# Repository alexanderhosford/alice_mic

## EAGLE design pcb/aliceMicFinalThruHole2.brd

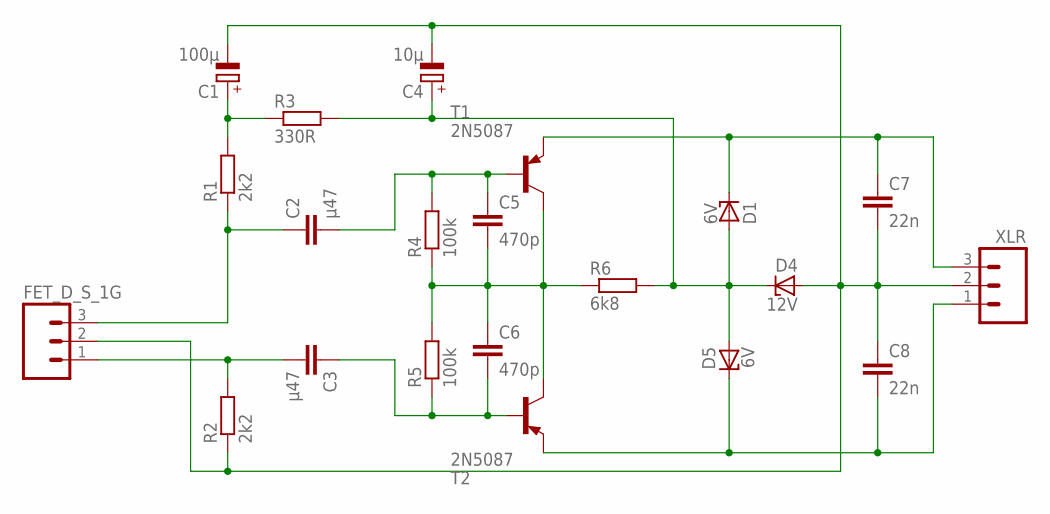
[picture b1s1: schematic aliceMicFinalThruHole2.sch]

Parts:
C1: 100µ; E3,5-8
C2, C3: µ47; C050-045X075
C4: 10µ; E2-4
C5, C6: 470p; C025-024X044
C7, C8: 22n; C025-024X044
D1, D5: 6V; ZD-5-SMALLSILK
D4: 12V; ZD-5-SMALLSILK
FET_D_S_1G: M033.5MM-PADS; 3.5MM_PADS
R1, R2: 2k2; 0207/2V
R3: 330R; 0207/2V
R4, R5: 100k; 0207/2V
R6: 6k8; 0207/2V
T1, T2: 2N5087; TO92-EBC
XLR: M033.5MM-PADS; 3.5MM_PADS

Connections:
GND: C1.-, C4.-, C7.2, C8.1, D4.A, FET_D_S_1G.2, R2.1, XLR.2
unnamed: C4.+, D1.A, D4.C, D5.A, R3.2, R6.2
unnamed: C5.2, C6.1, R4.1, R5.2, R6.1, T1.C, T2.C
unnamed: C7.1, D1.C, T1.E, XLR.3
unnamed: C8.2, D5.C, T2.E, XLR.1
unnamed: C2.2, C5.1, R4.2, T1.B
unnamed: C3.1, C6.2, R5.1, T2.B
unnamed: C1.+, R1.2, R3.1
unnamed: C2.1, FET_D_S_1G.3, R1.1
unnamed: C3.2, FET_D_S_1G.1, R2.2

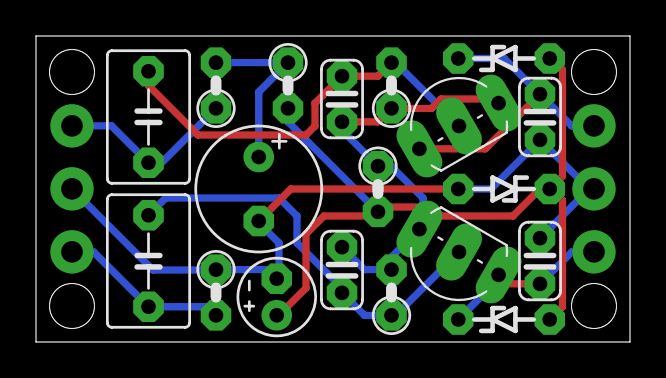
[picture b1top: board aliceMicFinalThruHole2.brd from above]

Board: 2 copper layers, 33.0 x 17.0 mm, 21 parts (0 on the bottom side), 10 nets.

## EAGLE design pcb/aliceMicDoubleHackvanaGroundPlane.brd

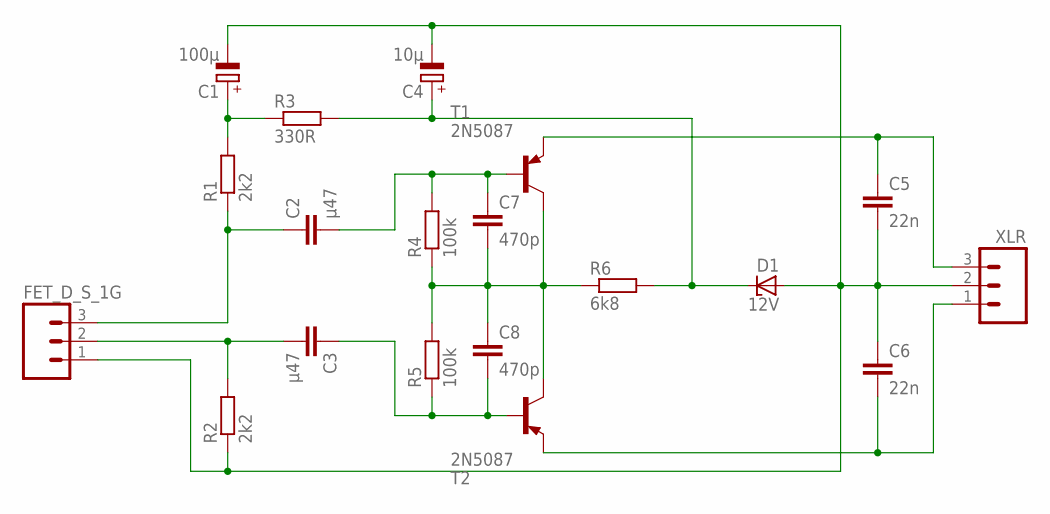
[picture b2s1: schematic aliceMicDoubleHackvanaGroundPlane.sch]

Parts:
C1: 100µ; E22-9
C2, C3: µ47; C050-055X075
C4: 10µ; E15-6
C5, C6: 22n; C025-024X044
C7, C8: 470p; C025-024X044
D1: 12V; 7MMGRIDZENER
FET_D_S_1G: M033.5MM-PADS; 3.5MM_PADS
R1, R2: 2k2; 0207/7
R3: 330R; 0207/7
R4, R5: 100k; 0207/7
R6: 6k8; 0207/7
T1, T2: 2N5087; TO92-EBC
XLR: M033.5MM-PADS; 3.5MM_PADS

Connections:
GND: C1.-, C4.-, C5.2, C6.1, D1.A, FET_D_S_1G.1, R2.1, XLR.2
unnamed: C4.+, D1.C, R3.2, R6.2
unnamed: C7.2, C8.1, R4.1, R5.2, R6.1, T1.C, T2.C
unnamed: C5.1, T1.E, XLR.3
unnamed: C6.2, T2.E, XLR.1
unnamed: C2.2, C7.1, R4.2, T1.B
unnamed: C3.1, C8.2, R5.1, T2.B
unnamed: C1.+, R1.2, R3.1
unnamed: C2.1, FET_D_S_1G.3, R1.1
unnamed: C3.2, FET_D_S_1G.2, R2.2

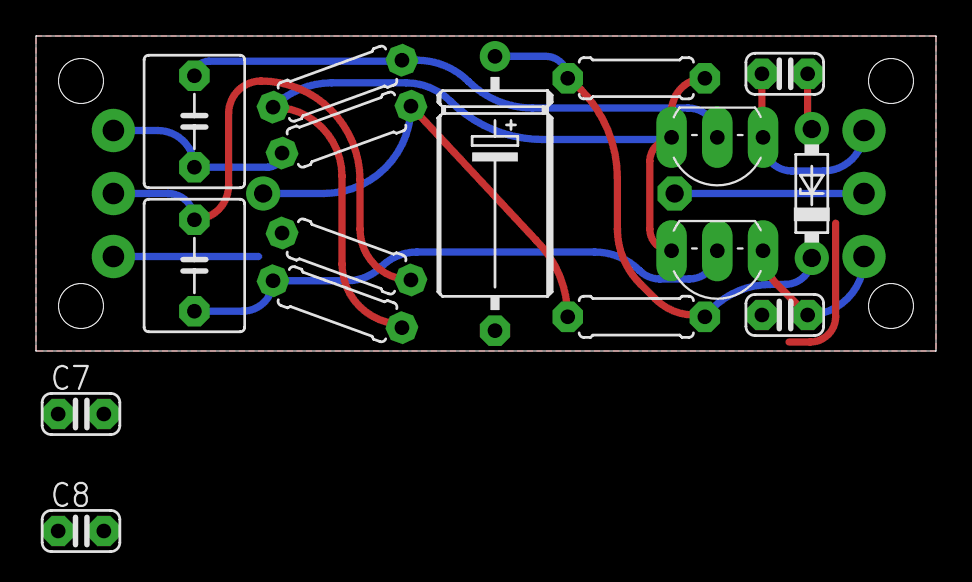
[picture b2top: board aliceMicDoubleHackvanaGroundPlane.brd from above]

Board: 2 copper layers, 50.0 x 17.5 mm, 19 parts (1 on the bottom side), 10 nets.

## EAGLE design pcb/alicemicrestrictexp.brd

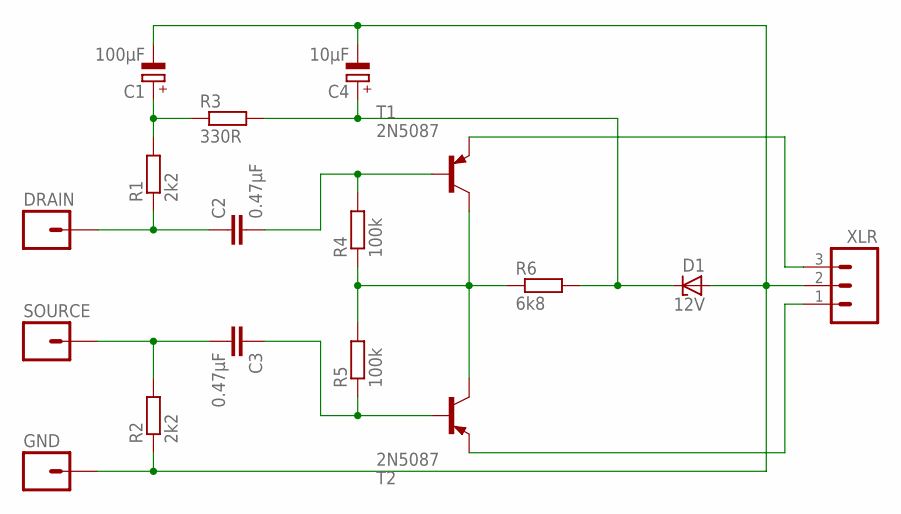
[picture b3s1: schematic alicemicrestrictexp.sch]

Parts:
C1: 100µF; E22-9
C2, C3: 0.47µF; C150-045X170
C4: 10µF; E15-6
D1: 12V; F126Z10
DRAIN: M01PTH; 1X01
GND: M01PTH; 1X01
R1, R2: 2k2; 0207/10
R3: 330R; 0207/10
R4, R5: 100k; 0207/10
R6: 6k8; 0207/10
SOURCE: M01PTH; 1X01
T1, T2: 2N5087; TO92-EBC
XLR: M03PTH; 1X03

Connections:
GND: C1.-, C4.-, D1.A, GND.1, R2.1, XLR.2
unnamed: C4.+, D1.C, R3.2, R6.2
unnamed: R4.1, R5.2, R6.1, T1.C, T2.C
unnamed: T1.E, XLR.3
unnamed: T2.E, XLR.1
unnamed: C2.2, R4.2, T1.B
unnamed: C3.1, R5.1, T2.B
unnamed: C1.+, R1.2, R3.1
unnamed: C2.1, DRAIN.1, R1.1
unnamed: C3.2, R2.2, SOURCE.1

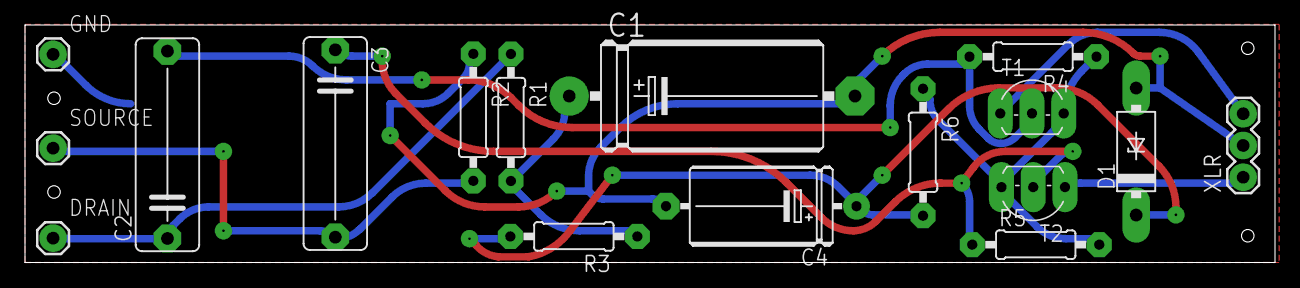
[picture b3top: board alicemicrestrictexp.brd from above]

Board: 2 copper layers, 100.0 x 19.0 mm, 17 parts (0 on the bottom side), 10 nets.

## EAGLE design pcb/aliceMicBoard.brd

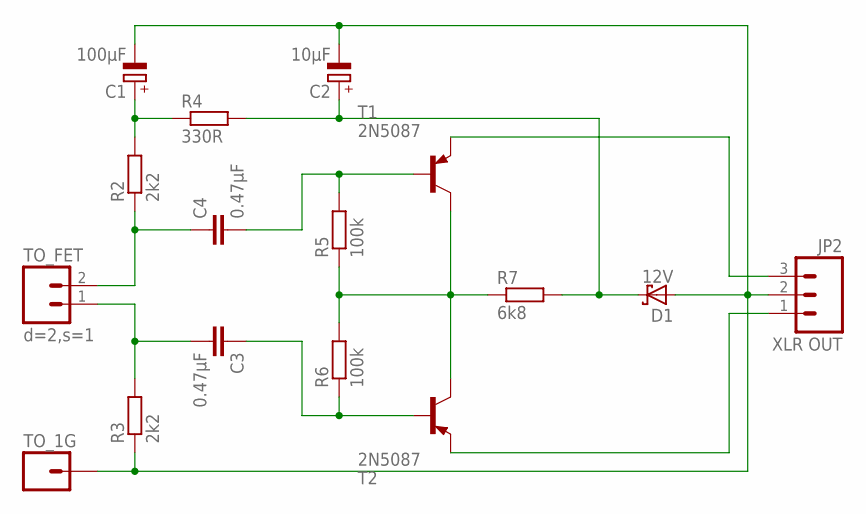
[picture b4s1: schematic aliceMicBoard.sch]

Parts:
C1: 100µF; E22-9
C2: 10µF; E15-6
C3, C4: 0.47µF; C150-054X183
D1: 12V; CB417-15
JP2: XLR OUT; SCREWTERMINAL-3.5MM-3
R2, R3: 2k2; 0207/10
R4: 330R; 0207/10
R5, R6: 100k; 0207/10
R7: 6k8; 0207/10
T1, T2: 2N5087; TO92-EBC
TO_1G: M01PTH_LONGPAD; 1X01_LONGPAD
TO_FET: d=2,s=1; SCREWTERMINAL-3.5MM-2

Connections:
unnamed: C1.-, C2.-, D1.A, JP2.2, R3.1, TO_1G.1
unnamed: C2.+, D1.C, R4.2, R7.2
unnamed: R5.1, R6.2, R7.1, T1.C, T2.C
unnamed: JP2.3, T1.E
unnamed: JP2.1, T2.E
unnamed: C4.2, R5.2, T1.B
unnamed: C3.1, R6.1, T2.B
unnamed: C1.+, R2.2, R4.1
unnamed: C4.1, R2.1, TO_FET.2
unnamed: C3.2, R3.2, TO_FET.1

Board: 2 copper layers, 16 parts (0 on the bottom side), 10 nets, no tracks yet.

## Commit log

2014-01-28 adding ignore file
2014-01-28 OpenScad files including code for 3D printed parts and overall construction diagrams
2014-01-28 rendered image files for PCBs
2014-01-28 Eagle files for schematics and PCBs
2014-01-28 gcode generated for 3D printed objects
2014-01-28 adding a blender file for a mesh object
2014-01-28 a sketchup object for representation of a pcb
2014-01-28 documentation for the project including original schematic and templates
2014-01-28 adding measurements file
2014-01-28 updating pcb housing
2014-01-28 updating main mic file
2014-01-28 adding pcb housing stl
2014-01-28 updating main mic file to include new pcb mount object
2014-01-29 renaming main file
2014-01-29 renaming board render file
2014-01-29 renaming clasp file
2014-01-29 renaming capsule cover files
2014-01-29 renaming sketchUp board render
2014-01-29 renaming rubber mount file
2014-01-29 Deleting unnecessary xlr pins file
2014-01-29 renaming rubber mount files
2014-01-29 Bringing tube out into own scad file for ease of editing.
    Grilles now integrated into single tube.
    Tube now reflects basic internal facing off for thread
2014-01-29 adding gcode for printing tests
2014-01-29 sketchUp file for board render
2014-01-30 Retaining only required TO72 STL object
2014-01-30 renaming mesh STL
2014-01-30 Updating element file with precision dimensions and all extrustions
2014-01-30 Files for a short threaded pin
2014-01-30 Removing ruler, updating element source
2014-01-30 Updating TO72 source
2014-01-30 Main file now reflects source changes re. Element
2014-01-30 Removal of unrequited STL files
2014-01-30 updating mesh object
2014-01-30 updating element object to use correct mesh
2014-01-30 Removing connector from tube object
2014-01-30 new file for end cap
2014-01-30 new file for neutrik connector trimming to diameter of tube
2014-01-30 Updating main render file
2014-01-30 added example of rounding
2014-01-31 Creating end cap object with mesh
2014-01-31 updating tube to allow for end cap object
2014-01-31 updating main file
2014-01-31 adding STL object for 1gΩ resistor
2014-01-31 Updating resistor object
    Removing legs
2014-01-31 Attempts at sorting out this to72 package model
2014-01-31 End cap object for CNC
2014-01-31 EagleUp output of latest PCB
2014-01-31 Updating main file with changes
2014-02-02 New version of small board for testing - includes vias instead of relying on component pins as vias
2014-02-02 Improving trace routing
2014-02-03 eagle log file
2014-02-03 output for CNC end cap object
2014-02-03 Changing colour of resistor object
2014-02-03 repositioning resistor next to capsule
2014-02-03 test files for Stephen to check out
2014-02-03 A repaired STL object produced by NetFabb Basic
2014-02-03 A Repaired STL object produced by blender
2014-02-03 Updating get file to use new blender repaired object
2014-02-03 Adding pcb housing back into the view
2014-02-03 Renaming STL file to indicate repair source
2014-02-04 Ignoring docs folder
2014-02-04 test cylinder to gauge height
2014-02-04 updating gitignore
2014-02-04 readding docs
2014-02-04 New model of a to72 package FET
2014-02-04 Attempting rounding of capsule
2014-02-04 Attempt at modifying get stl
2014-02-04 updating epf file
2014-02-04 deleting useless 3d models.
2014-02-05 Removing unwanted pcb files
2014-02-05 Grouping files
2014-02-05 Grouping component files
2014-02-05 Removing unwanted files
2014-02-05 New rubber mount object, with thin and thick wall thicknesses

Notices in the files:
parts and their libraries:
SparkFun: Licensing: CC v3.0 Share-Alike You are welcome to use this library for commercial purposes.
